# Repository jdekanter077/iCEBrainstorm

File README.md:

# iCEBrainstorm

A STM32F412 MCU with a iCE40UP5K FPGA on a compact dev board.

You will need STMCubeMX, VSCode with the STM32Cube Extension and STMCubeProgrammer to program the STM.

<!-- You can use [apio](https://github.com/FPGAwars/apio) to synthesise a design and upload the firmware to the FPGA using a [online dfu-uploader](https://devanlai.github.io/webdfu/dfu-util/) (easier) -->

<!-- You will need to use the [oss-cad-suite](https://github.com/YosysHQ/oss-cad-suite-build) to to synthesise your design and upload the bitstream to the FPGA.  -->
You can use apio to synthesize and upload your hdl on the FPGA. Refer to [apio support](#apio-support) on how to configure apio to support the iCEBrainstorm board.

## Basic Structure
The STM32 Microcontroller and the iCE40 FPGA share one PCB and have some connections between them to communicate.
They can be programmed through their respective USB-C Port.
There are some switches to select the "program mode" for both the STM and the FPGA.

The code and bootloader of the SMT are stored inside the SMT IC, but the code and bootloader of the FPGA are stored on an external SPI Flash IC. 

There is also an gyrosensor on board. For more documentation, go look at the KiCAD files.

<!--  -->

## How to Program:
Both the STM and the FPGA use a "Bootloader" to re-program themselfes. This makes the device visible to your computer and puts it in "program mode".

### STM32
The STM32 relies on its build-in bootloader to program itself via USB.
The bootloader is selected by switching the ```BOOT0``` Switch and ```RESET```-ing the SMT:
- Set the ```BOOT0``` Switch
- press ```RESET STM``` or plug in the cable
- The STM is now in DFU-mode, and can be programmed with STM32CubeProgrammer (or other software)
- In CubeProgrammer: select USB and click connect

- Click ```Open File``` and select your ```.elf``` file

- Click ```Download```

- Reset the ```BOOT0``` Switch.
- press ```RESET STM``` and your code should run.

### ICE40 FPGA

The FPGA relies on the [no2 bootloader](https://github.com/psychogenic/no2bootloader/tree/master), which is stored on the SPI-Flash IC.
The bootloader is selected by switching the ```FBOOT``` switch and ```RESET```-ing the FPGA, and then putting the ```FBOOT``` switch back.
Check if the ```CDONE``` LED at the top of the board is on.

- Set the ```FBOOT``` Switch
- press ```RESET FPGA``` or plug in the cable
- Reset the ```BOOT0``` Switch.
- Check if the ```CDONE``` LED at the top of the board is on.
- The FPGA is now in DFU-mode, and can be programmed with 
```apio upload``` or using ```dfu-util```

<!-- - run ```dfu-util -l``` to list all dfu devices. -->
<!-- example output: 
```Found DFU: [1d50:6146] ver=0006, devnum=12, cfg=1, intf=0, path="", alt=1, name="RISC-V firmware", serial="e464bc68932e5839"
Found DFU: [1d50:6146] ver=0006, devnum=12, cfg=1, intf=0, path="", alt=0, name="iCE40 bitstream", serial="e464bc68932e5839"
``` -->
<!-- - run ```dfu-util -d 1d50:6146 -a 0 -D hardware.bin``` to flash your bitstream on the FPGA. Maybe You have to replace the ```1d50:6146```-number with what you see on your terminal. -->
- you can run ```apio devices usb``` to list all dfu devices and verify that everything works.
- run ```apio upload``` to synthesize and upload the verilog code.

-  To edit your HDL code, take a look at the examples in [software/FPGA](./software/FPGA)

### APIO Support
[apio](https://github.com/FPGAwars/apio) is a open-source FPGA Toolchain, which will help us synthesize HDL code.
Make sure you have a recent version of apio installed! You can uninstall and install again to update.
- Install apio using ```pip install apio```
- edit ```~/.apio/packages/definitions/boards.jsonc``` and add this snippet:
```
  // https://github.com/jdekanter077/iCEBrainstorm
  "iCEBrainstorm": {
    "legacy-name": "iCEBrainstorm",
    "description": "iCEBrainstorm by jdk",
    "fpga-id": "ice40up5k-sg48",
    "programmer": {
      "id": "dfu"
    },
    "usb": {
      "vid": "1d50",
      "pid": "6146"
    }
  },
```

This will add apio support for the iCEBrainstorm board.
-  to create a new project, run ```apio create -b iCEBrainstorm```
-  edit your HDL code, take a look at the examples in [software/FPGA](./software/FPGA)

### Bootloader
The Bootloader is preinstalled by Joël and should not have to be touched.
Check out [bootloader/README.md](./software/FPGA/bootloader/README.md) for more information.

## Setting up a blank Project
### STM
- Open CubeMX and select ```File -> New Project```.
- In ```Commercial Part Number```, Type ```STM32F412RET6TR``` and select ```Start Project```.

- Select ```RCC_MCO_2``` on ```PB9``` to provide a Clock signal to the FPGA
- Select your desired pins, for example ```PB5```, which is connected to the on-board LED and select ```GPIO_Output```.

- On the left Pane in ```System Core -> GPIO -> PB5``` set a user label, for example ```OUT_STM```

- Set the Input Clock to Cyrstal Oscillator in ```System Core -> RCC```

- Got to ```Clock Configuration``` at the top and set the Input Frequency of the Clock to 16 MHz

- Go to ```Project Manager``` on the top.
Make sure to select ```CMake``` as the ```Toolchain / IDE```.

Make sure to set ```Generate ... as pair of '.c/.h' files ...```

- Save your project and click ```GENRATE CODE``` in the top right and open the folder in VSCode

- Make sure to not miss the notification to "configure CMake Projects as STM32 Projects". click Yes.

- Select a Preset from the Popup (Debug)
- Edit the Code, for example, add blinky loop in ```Core/Src/main.c```
- ```line 98```:

```
/* USER CODE BEGIN WHILE */
while (1)
  {
    HAL_GPIO_TogglePin(OUT_STM_GPIO_Port, OUT_STM_Pin);
    HAL_Delay(100);
    /* USER CODE END WHILE */

    /* USER CODE BEGIN 3 */
  }
  /* USER CODE END 3 */
}
```
- To Compile the code, go to ```Run & Debug -> Run & Debug -> STM32Cube: STLink GDB Server```

- This will compile the code, and try to start a "debugger", which is not available and gives a error. The Code should still be compiled correctly!
- Check if you have a ```.elf``` file in ```build/Debug/```. Upload this to the iCEBrainstorm using the steps described in [how-to-programm](#how-to-program)

## Clock
The STM and the FPGA are relatively independent from each other, with one slight caveat:
The STM32 is responsible for providing the FPGA with a Clock signal. The no2-bootloader of the FPGA relies on this clock source, and will not work without it. 

This clock can of course be used in your FPGA design as well.

### How to provide the clock 
- In cubeMX, go to ```PC9``` and select ```RCC_MCO_2```

- Generate Code, open the folder in STMCubeIDE or VSCode, compile, and upload using STMCubeProgrammer.
- Done!

## FPGA Pinout Description:
These informations should be in every ```main.pcf``` file.

| Description | FPGA Pin | Usage |
| --- | ---- | ---- |
| clk_i | 20  | 16 MHz Clock, provided by the STM32 | 
| btn_0 | 31 | left button | 
| btn_1 | 32 | right button | 
| in_0 | 34 | Input Switch and/or GPIO | 
| in_1 | 35 | Input Switch and/or GPIO | 
| in_2 | 36 | Input Switch and/or GPIO | 
| in_3 | 37 | Input Switch and/or GPIO | 
| out_0 | 25  | LED | 
| out_1 | 26  | LED | 
| out_2 | 27  | LED | 
| out_3 | 28  | LED | 
| io_0 | 47  | GPIO | 
| io_1 | 42  | GPIO | 
| io_2 | 38  | GPIO | 
| io_3 | 23  | GPIO | 
| rgb_0 | 39 | RGB LED and/or GPIO | 
| rgb_1 | 40 | RGB LED and/or GPIO | 
| rgb_2 | 41 | RGB LED and/or GPIO | 
| uart_tx | 2  | uart output (STM RX <- FPGA TX) | 
| uart_rx | 3  | uart input (STM TX -> FPGA RX) | 
| scl | 19 | I2C Clock | 
| sda | 18 | I2C Data | 

# Examples

## FPGA & STM: Morse Encoder
This project implements Morse encoder. The FPGA encodes the Morse Code, and sends the encoded character over UART to the STM.
The STM then sends the recieved character over USB to the host machine.

- upload ```./software/STM/uart_serial_bridge``` to the STM.
- upload ```./software/FPGA/morse_uart``` to the FPGA.
- open a serial monitor and have fun!

for details: take a look at the [Readme](./software/FPGA/morse_uart/README.md)

## STM: uart-serial Bridge

This project implements a UART-Serial bridge. The STM sends all recieved uart messages over usb to the host machine, and sends all recieved usb messages over usb to the FPGA.
This is done by using an Interrupt-driven approach.

snippet:

## FPGA: bram
[bram](./software/FPGA/bram)

This example of how to instintiate a one of the build-in BRAMs on the FPGA is based on [this repo](https://github.com/damdoy/ice40_ultraplus_examples/tree/master/bram) and on the [online documentation](https://www.latticesemi.com/~/media/LatticeSemi/Documents/ApplicationNotes/MO/MemoryUsageGuideforiCE40Devices.pdf)
It uses the switches IN0-IN3 as input "data" and loads it into the bram using btn0. Using btn1, the "data" can then be displayed on the leds.

# Author
Joël de Kanter

# License

This repository is primarily licensed under the GNU General Public License v3.0.

Exceptions:
- STM32CubeMX-generated files are licensed under STMicroelectronics'
  STM32Cube firmware license (see file headers).
- The NO2 bootloader firmware is licensed under GPL-3.0-or-later
- Some third-party components may be licensed under MIT or CERN OHL v2.

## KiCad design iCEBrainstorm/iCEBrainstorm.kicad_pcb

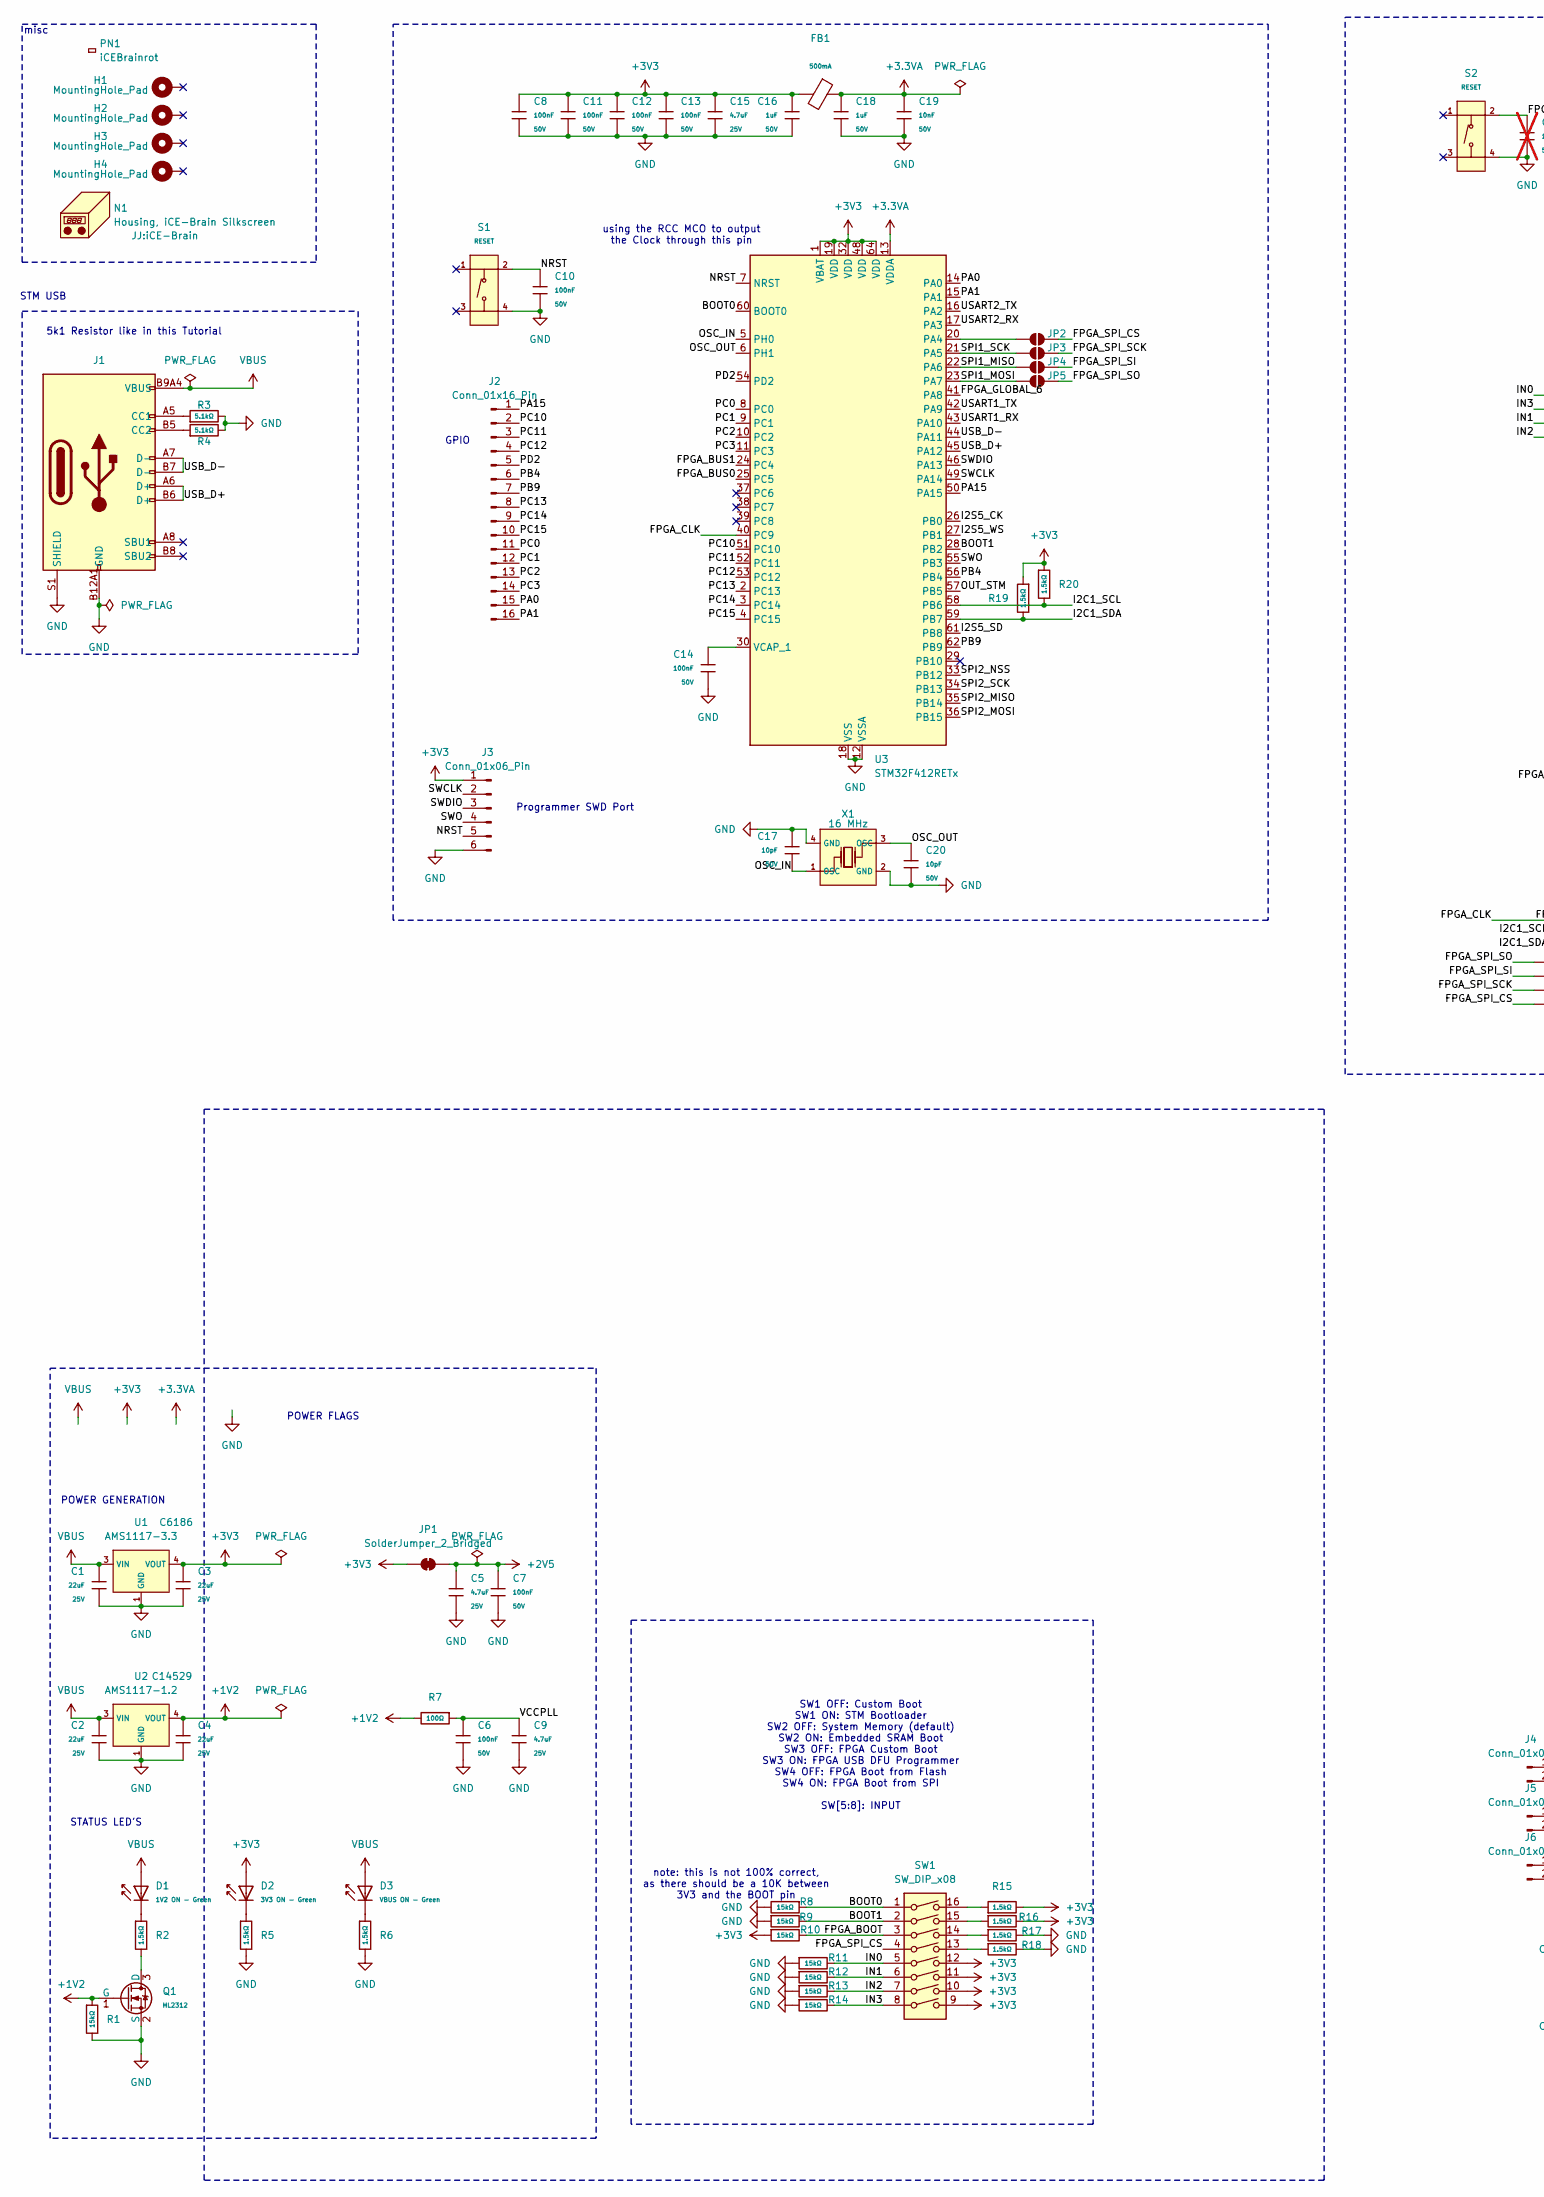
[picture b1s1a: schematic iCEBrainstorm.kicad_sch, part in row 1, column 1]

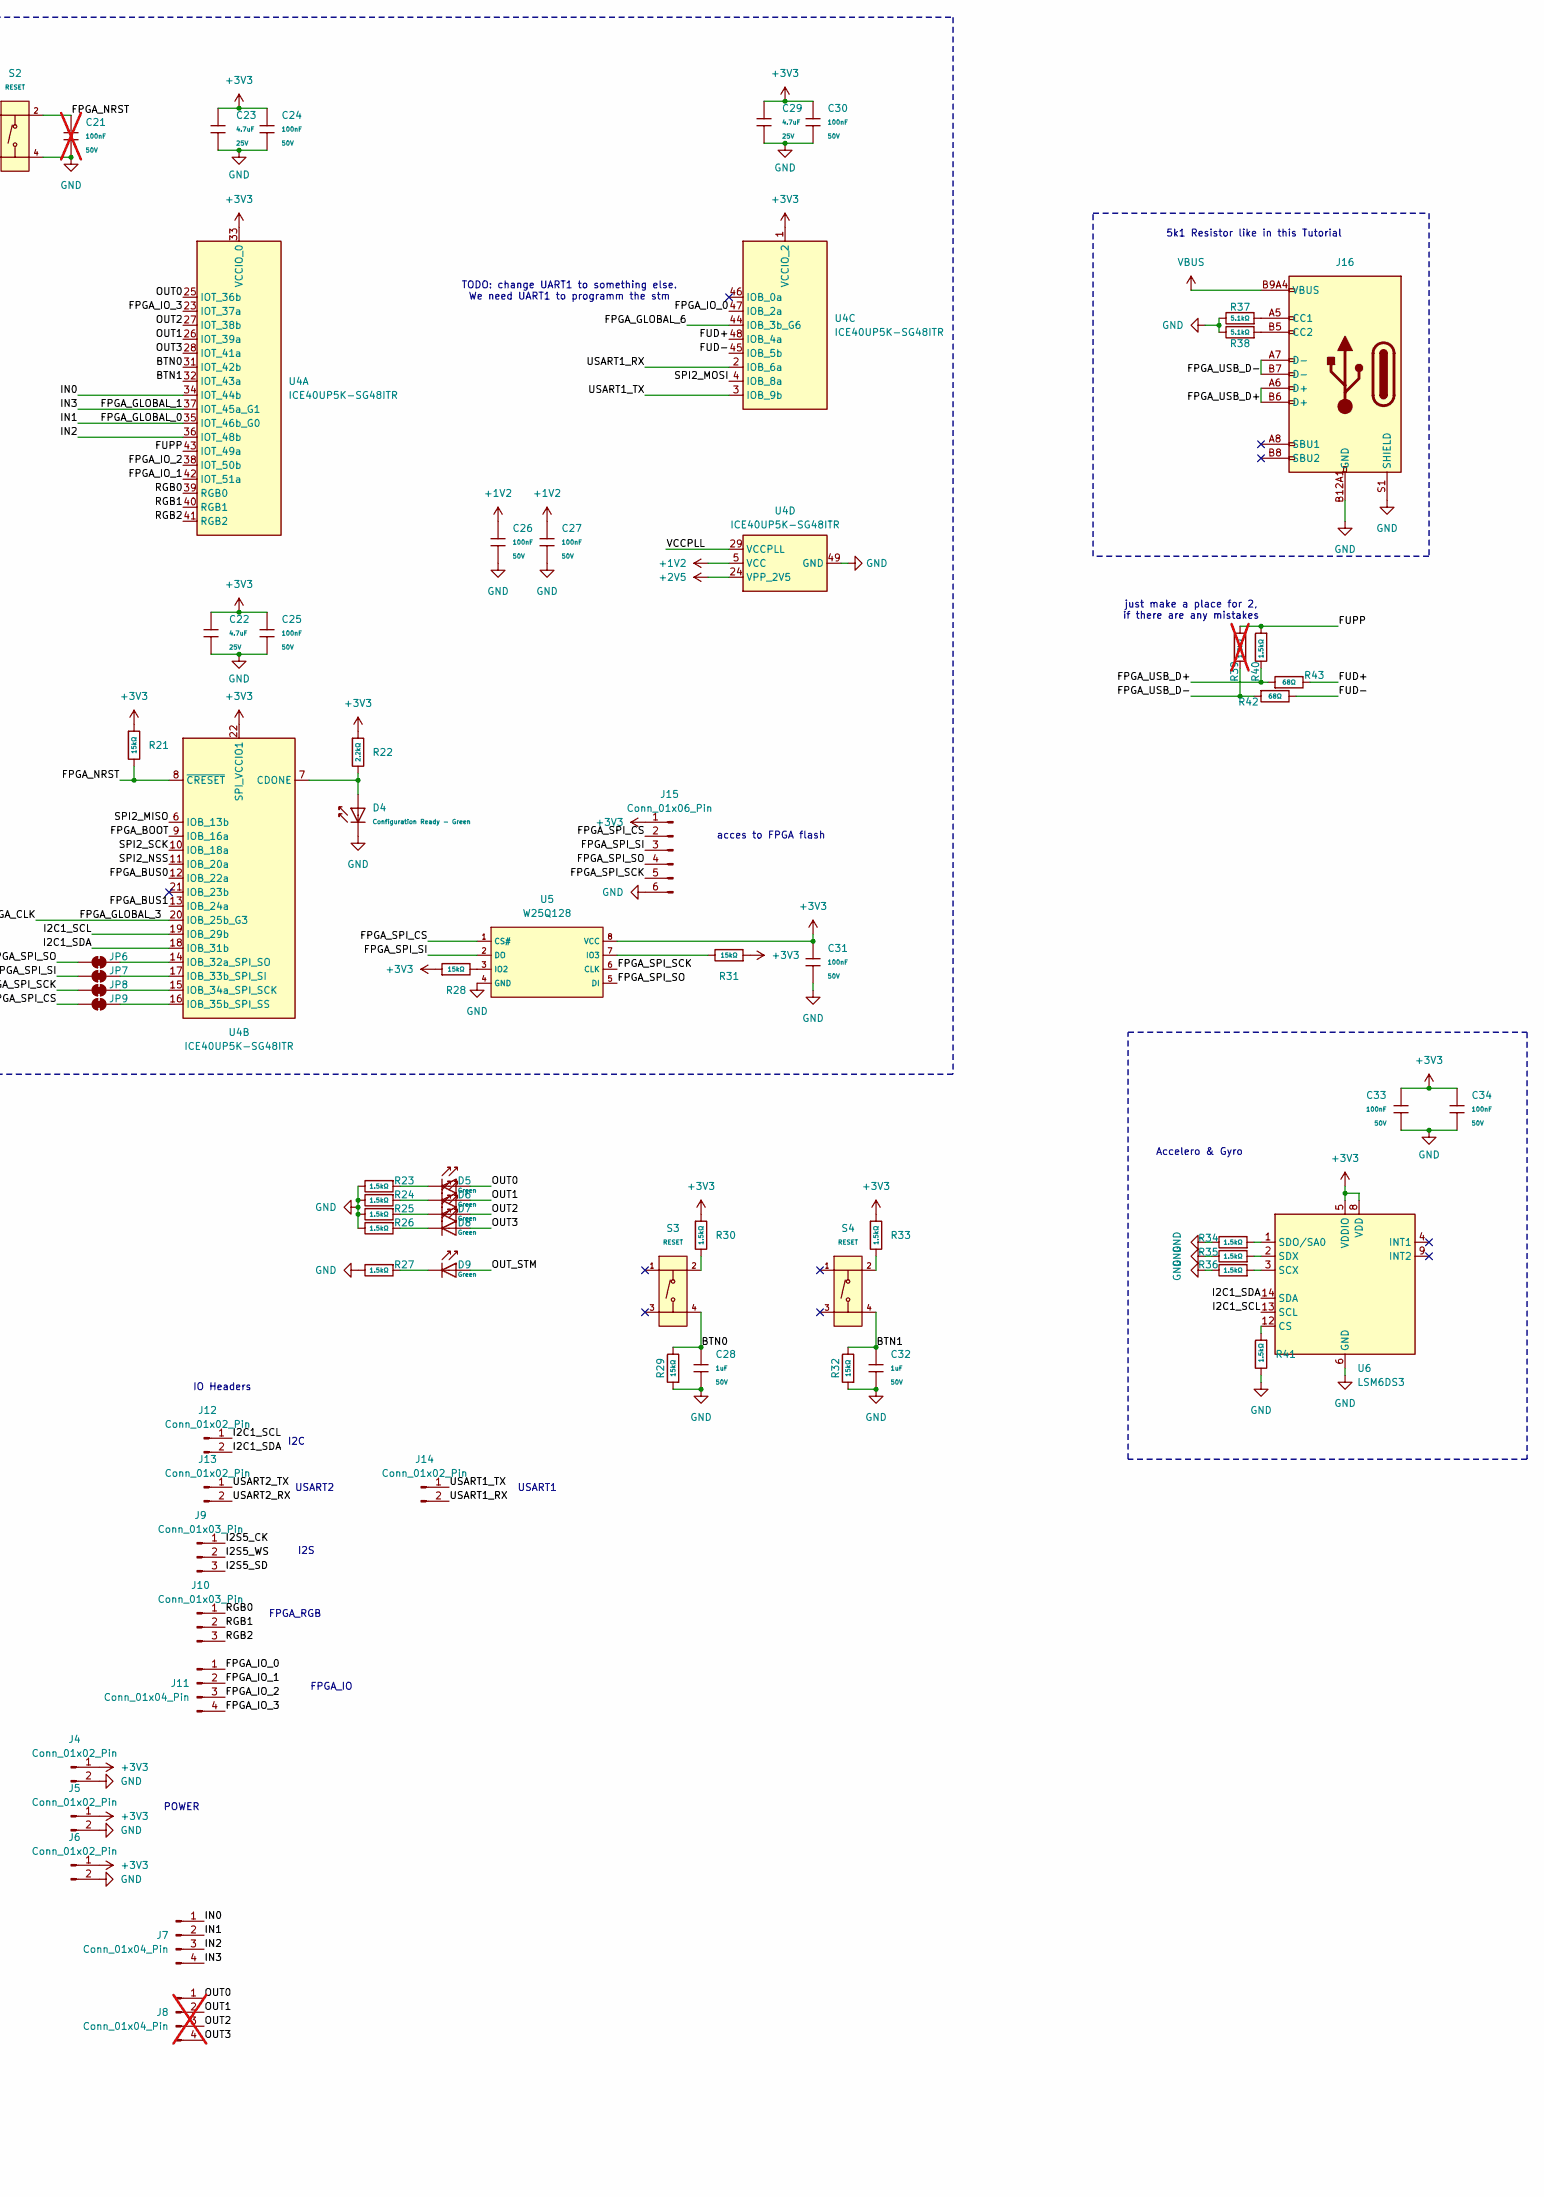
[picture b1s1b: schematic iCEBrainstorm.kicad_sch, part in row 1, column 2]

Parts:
C1, C2, C3, C4: 22uF; C_0805; Voltage Rated 25V; Tolerance ±20%; Part CL21A226MAQNNNE; LCSC C45783
C5, C9, C15, C22, C23, C29: 4.7uF; C_0805; Voltage Rated 25V; Tolerance ±10%; Part CL21A475KAQNNNE; LCSC C1779
C6, C7, C8, C10, C11, C12, C13, C14, C24, C25, C26, C27, C30, C31, C33, C34: 100nF; C_0603; Voltage Rated 50V; Tolerance ±10%; Part CC0603KRX7R9BB104; LCSC C14663
C16, C18, C28, C32: 1uF; C_0603; Voltage Rated 50V; Tolerance ±10%; Part CL10A105KB8NNNC; LCSC C15849
C17, C20: 10pF; C_0603; Voltage Rated 50V; Tolerance ±5%; Part CL10C100JB8NNNC; LCSC C1634
C19: 10nF; C_0603; Voltage Rated 50V; Tolerance ±10%; Part 0603B103K500NT; LCSC C57112
C21: 100nF; C_0603; Voltage Rated 50V; Tolerance ±10%; Part CC0603KRX7R9BB104; LCSC C14663; not fitted
D1: 1V2 ON - Green; D_0805; Part KT-0805G; LCSC C2297
D2: 3V3 ON - Green; D_0805; Part KT-0805G; LCSC C2297
D3: VBUS ON - Green; D_0805; Part KT-0805G; LCSC C2297
D4: Configuration Ready - Green; D_0805; Part KT-0805G; LCSC C2297
D5, D6, D7, D8, D9: Green; D_0805; Part KT-0805G; LCSC C2297
FB1: FB_0805; Current Rating 500mA; Tolerance ±25%; Part GZ2012D601TF; LCSC C1017
H1, H2, H3, H4: MountingHole_Pad; MountingHole_2.7mm_Pad
J1, J16: Connector, USB-TYPE-C-16P; TYPE-C-SMD_HX-TYPE-C-16PIN; LCSC C2927039
J2: Conn_01x16_Pin; PinHeader_1x16_P2.54mm_Vertical
J3, J15: Conn_01x06_Pin; PinHeader_1x06_P2.54mm_Vertical
J4, J5, J6, J12, J13, J14: Conn_01x02_Pin; PinHeader_1x02_P2.54mm_Vertical
J7, J11: Conn_01x04_Pin; PinHeader_1x04_P2.54mm_Vertical
J8: Conn_01x04_Pin; PinHeader_1x04_P2.54mm_Vertical; not fitted
J9, J10: Conn_01x03_Pin; PinHeader_1x03_P2.54mm_Vertical
JP1, JP6, JP7, JP8, JP9: SolderJumper_2_Bridged; SolderJumper-2_P1.3mm_Bridged_RoundedPad1.0x1.5mm
JP2, JP3, JP4, JP5: SolderJumper_2_Open; SolderJumper-2_P1.3mm_Open_RoundedPad1.0x1.5mm
N1: Housing, iCE-Brain Silkscreen; iCE-Brain
PN1: iCEBrainrot; Part_Num_JLCPCB
Q1: HL2312; Q_SOT-23; Part HL2312; LCSC C28646272
R1, R8, R9, R10, R11, R12, R13, R14, R21, R28, R29, R31, R32: 15kΩ; R_0603; Overload Voltage (Max) 75V; Tolerance ±1%; Part 0603WAF1502T5E; LCSC C22809
R2, R5, R6, R15, R16, R17, R18, R19, R20, R23, R24, R25, R26, R27, R30, R33, R34, R35, R36, R40, R41: 1.5kΩ; R_0603; Overload Voltage (Max) 75V; Tolerance ±1%; Part 0603WAF1501T5E; LCSC C22843
R3, R4, R37, R38: 5.1kΩ; R_0603; Overload Voltage (Max) 75V; Tolerance ±1%; Part 0603WAF5101T5E; LCSC C23186
R7: 100Ω; R_0603; Overload Voltage (Max) 75V; Tolerance ±1%; Part 0603WAF1000T5E; LCSC C22775
R22: 2.2kΩ; R_0603; Overload Voltage (Max) 75V; Tolerance ±1%; Part 0603WAF2201T5E; LCSC C4190
R39: 1.5kΩ; R_0603; Overload Voltage (Max) 75V; Tolerance ±1%; Part 0603WAF1501T5E; LCSC C22843; not fitted
R42, R43: 68Ω; R_0603; Overload Voltage (Max) 75V; Tolerance ±1%; Part 0603WAF680JT5E; LCSC C27592
S1, S2, S3, S4: RESET; SW-SMD_4P-L5.1-W5.1-P3.70-LS6.5-TL-2; Voltage Rating (Dc) 12V; Part TS-1187A-B-A-B; LCSC C318884
SW1: SW_DIP_x08; SW_DIP_SPSTx08_Slide_6.7x21.88mm_W7.62mm_P2.54mm_LowProfile
U1: AMS1117-3.3; SOT-223-3_L6.5-W3.4-P2.30-LS7.0-BR; Output Voltage 3.3V; Dropout Voltage 1.3V@(800mA); Part AMS1117-3.3; LCSC C6186
U2: AMS1117-1.2; SOT-223-3_L6.5-W3.4-P2.30-LS7.0-BR; Output Voltage 3.3V; Dropout Voltage 1.3V@(800mA); Part AMS1117-3.3; LCSC C14529
U3: STM32F412RETx; LQFP-64_10x10mm_P0.5mm
U4: ICE40UP5K-SG48ITR; QFN-48-1EP_7x7mm_P0.5mm_EP5.6x5.6mm
U5: W25Q128; SOIC-8_L5.3-W5.3-P1.27-LS8.0-BL; Part W25Q128JVSIQ; LCSC C97521
U6: LSM6DS3; LGA-14_3x2.5mm_P0.5mm_LayoutBorder3x4y
X1: 16 MHz; OSC-SMD_4P-L3.2-W2.5-BL; Frequency Tolerance ±10ppm; Part X322516MLB4SI; LCSC C13738

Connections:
+1V2: C4.2, C26.1, C27.1, Q1.1 (G), R1.1, R7.2, U2.2 (VOUT), U2.4 (VOUT), U4.5 (VCC), U4.30 (VCC)
+2V5: C5.1, C7.1, JP1.2 (B), U4.24 (VPP_2V5)
+3.3VA: C18.1, C19.1, FB1.1, U3.13 (VDDA)
+3V3: C3.2, C8.1, C11.1, C12.1, C13.1, C15.1, C16.1, C22.1, C23.1, C24.1, C25.1, C29.1, C30.1, C31.1, C33.1, C34.1, D2.2, FB1.2, J3.1, J4.1, J5.1, J6.1, J15.1, JP1.1 (A), R10.1, R15.2, R16.2, R19.1, R20.1, R21.1, R22.1, R28.1, R30.1, R31.1, R33.1, SW1.9, SW1.10, SW1.11, SW1.12, U1.2 (VOUT), U1.4 (VOUT), U3.1 (VBAT), U3.19 (VDD), U3.32 (VDD), U3.48 (VDD), U3.64 (VDD), U4.1 (VCCIO_2), U4.22 (SPI_VCCIO1), U4.33 (VCCIO_0), U5.8 (VCC), U6.5 (VDDIO), U6.8 (VDD)
/BOOT0: R8.1, SW1.1, U3.60 (BOOT0)
/BOOT1: R9.2, SW1.2, U3.28 (PB2)
/BTN0: C28.1, R29.2, S3.4 (D), U4.31 (IOT_42b)
/BTN1: C32.1, R32.2, S4.4 (D), U4.32 (IOT_43a)
/FPGA_BOOT: R10.2, SW1.3, U4.9 (IOB_16a)
/FPGA_BUS0: U3.25 (PC5), U4.12 (IOB_22a)
/FPGA_BUS1: U3.24 (PC4), U4.13 (IOB_24a)
/FPGA_CLK: U3.40 (PC9), U4.20 (IOB_25b_G3)
/FPGA_GLOBAL_0: J7.2, R12.2, SW1.6, U4.35 (IOT_46b_G0)
/FPGA_GLOBAL_1: J7.4, R14.2, SW1.8, U4.37 (IOT_45a_G1)
/FPGA_GLOBAL_6: U3.41 (PA8), U4.44 (IOB_3b_G6)
/FPGA_IO_0: J11.1, U4.47 (IOB_2a)
/FPGA_IO_1: J11.2, U4.42 (IOT_51a)
/FPGA_IO_2: J11.3, U4.38 (IOT_50b)
/FPGA_IO_3: J11.4, U4.23 (IOT_37a)
/FPGA_NRST: C21.1, R21.2, S2.2 (B), U4.8 (~CRESET)
/FPGA_SPI_CS: J15.2, JP2.2 (B), JP9.1 (A), SW1.4, U5.1 (CS#)
/FPGA_SPI_SCK: J15.5, JP3.2 (B), JP8.1 (A), U5.6 (CLK)
/FPGA_SPI_SI: J15.3, JP4.2 (B), JP7.1 (A), U5.2 (DO)
/FPGA_SPI_SO: J15.4, JP5.2 (B), JP6.1 (A), U5.5 (DI)
/FPGA_USB_D+: J16.A6 (D+), J16.B6 (D+), R40.2, R43.1
/FPGA_USB_D-: J16.A7 (D-), J16.B7 (D-), R39.2, R42.1
/FUD+: R43.2, U4.48 (IOB_4a)
/FUD-: R42.2, U4.45 (IOB_5b)
/FUPP: R39.1, R40.1, U4.43 (IOT_49a)
/I2C1_SCL: J12.1, R20.2, U3.58 (PB6), U4.19 (IOB_29b), U6.13 (SCL)
/I2C1_SDA: J12.2, R19.2, U3.59 (PB7), U4.18 (IOB_31b), U6.14 (SDA)
/I2S5_CK: J9.1, U3.26 (PB0)
/I2S5_SD: J9.3, U3.61 (PB8)
/I2S5_WS: J9.2, U3.27 (PB1)
/IN0: J7.1, R11.2, SW1.5, U4.34 (IOT_44b)
/IN2: J7.3, R13.2, SW1.7, U4.36 (IOT_48b)
/NRST: C10.1, J3.5, S1.2 (B), U3.7 (NRST)
/OSC_IN: C17.2, U3.5 (PH0), X1.1 (OSC)
/OSC_OUT: C20.1, U3.6 (PH1), X1.3 (OSC)
/OUT0: D5.2, J8.1, U4.25 (IOT_36b)
/OUT1: D6.2, J8.2, U4.26 (IOT_39a)
/OUT2: D7.2, J8.3, U4.27 (IOT_38b)
/OUT3: D8.2, J8.4, U4.28 (IOT_41a)
/OUT_STM: D9.2, U3.57 (PB5)
/PA0: J2.15, U3.14 (PA0)
/PA1: J2.16, U3.15 (PA1)
/PA15: J2.1, U3.50 (PA15)
/PB4: J2.6, U3.56 (PB4)
/PB9: J2.7, U3.62 (PB9)
/PC0: J2.11, U3.8 (PC0)
/PC1: J2.12, U3.9 (PC1)
/PC2: J2.13, U3.10 (PC2)
/PC3: J2.14, U3.11 (PC3)
/PC10: J2.2, U3.51 (PC10)
/PC11: J2.3, U3.52 (PC11)
/PC12: J2.4, U3.53 (PC12)
/PC13: J2.8, U3.2 (PC13)
/PC14: J2.9, U3.3 (PC14)
/PC15: J2.10, U3.4 (PC15)
/PD2: J2.5, U3.54 (PD2)
/RGB0: J10.1, U4.39 (RGB0)
/RGB1: J10.2, U4.40 (RGB1)
/RGB2: J10.3, U4.41 (RGB2)
/SPI1_MISO: JP4.1 (A), U3.22 (PA6)
/SPI1_MOSI: JP5.1 (A), U3.23 (PA7)
/SPI1_SCK: JP3.1 (A), U3.21 (PA5)
/SPI2_MISO: U3.35 (PB14), U4.6 (IOB_13b)
/SPI2_MOSI: U3.36 (PB15), U4.4 (IOB_8a)
/SPI2_NSS: U3.33 (PB12), U4.11 (IOB_20a)
/SPI2_SCK: U3.34 (PB13), U4.10 (IOB_18a)
/SWCLK: J3.2, U3.49 (PA14)
/SWDIO: J3.3, U3.46 (PA13)
/SWO: J3.4, U3.55 (PB3)
/USART1_RX: J14.2, U3.43 (PA10), U4.2 (IOB_6a)
/USART1_TX: J14.1, U3.42 (PA9), U4.3 (IOB_9b)
/USART2_RX: J13.2, U3.17 (PA3)
/USART2_TX: J13.1, U3.16 (PA2)
/USB_D+: J1.A6 (D+), J1.B6 (D+), U3.45 (PA12)
/USB_D-: J1.A7 (D-), J1.B7 (D-), U3.44 (PA11)
/VCCPLL: C6.1, C9.1, R7.1, U4.29 (VCCPLL)
GND: C1.1, C2.1, C3.1, C4.1, C5.2, C6.2, C7.2, C8.2, C9.2, C10.2, C11.2, C12.2, C13.2, C14.1, C15.2, C16.2, C17.1, C18.2, C19.2, C20.2, C21.2, C22.2, C23.2, C24.2, C25.2, C26.2, C27.2, C28.2, C29.2, C30.2, C31.2, C32.2, C33.2, C34.2, D4.1, J1.A12B1 (GND), J1.B12A1 (GND), J1.S1 (SHIELD), J3.6, J4.2, J5.2, J6.2, J15.6, J16.A12B1 (GND), J16.B12A1 (GND), J16.S1 (SHIELD), Q1.2 (S), R1.2, R3.2, R4.2, R5.2, R6.2, R8.2, R9.1, R11.1, R12.1, R13.1, R14.1, R17.2, R18.2, R23.2, R24.2, R25.2, R26.2, R27.2, R29.1, R32.1, R34.2, R35.2, R36.2, R37.2, R38.2, R41.2, S1.4 (D), S2.4 (D), U1.1 (GND), U2.1 (GND), U3.12 (VSSA), U3.18 (VSS), U3.31 (VSS), U3.47 (VSS), U3.63 (VSS), U4.49 (GND), U5.4 (GND), U6.6 (GND), U6.7 (GND), X1.2 (GND), X1.4 (GND)
unnamed: D1.1, R2.1
unnamed: D2.1, R5.1
unnamed: D3.1, R6.1
unnamed: D5.1, R23.1
unnamed: D6.1, R24.1
unnamed: D7.1, R25.1
unnamed: D8.1, R26.1
unnamed: D9.1, R27.1
unnamed: J1.A5 (CC1), R3.1
unnamed: J1.B5 (CC2), R4.1
unnamed: J16.A5 (CC1), R37.1
unnamed: J16.B5 (CC2), R38.1
unnamed: JP2.1 (A), U3.20 (PA4)
unnamed: JP6.2 (B), U4.14 (IOB_32a_SPI_SO)
unnamed: JP7.2 (B), U4.17 (IOB_33b_SPI_SI)
unnamed: JP8.2 (B), U4.15 (IOB_34a_SPI_SCK)
unnamed: JP9.2 (B), U4.16 (IOB_35b_SPI_SS)
unnamed: Q1.3 (D), R2.2
unnamed: R15.1, SW1.16
unnamed: R16.1, SW1.15
unnamed: R17.1, SW1.14
unnamed: R18.1, SW1.13
unnamed: R30.2, S3.2 (B)
unnamed: R33.2, S4.2 (B)
unnamed: C14.2, U3.30 (VCAP_1)
unnamed: D4.2, R22.2, U4.7 (CDONE)
unnamed: R28.2, U5.3 (IO2)
unnamed: R31.2, U5.7 (IO3)
unnamed: R41.1, U6.12 (CS)
unnamed: R36.1, U6.3 (SCX)
unnamed: R34.1, U6.1 (SDO/SA0)
unnamed: R35.1, U6.2 (SDX)
VBUS: C1.2, C2.2, D1.2, D3.2, J1.A9B4 (VBUS), J1.B9A4 (VBUS), J16.A9B4 (VBUS), J16.B9A4 (VBUS), U1.3 (VIN), U2.3 (VIN)

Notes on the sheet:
GPIO
POWER GENERATION
acces to FPGA flash
FPGA_IO
Programmer SWD Port
misc
I2S
IO Headers
5k1 Resistor like in this Tutorial
TODO: change UART1 to something else. We need UART1 to programm the stm
I2C
USART2
Accelero & Gyro
POWER FLAGS
note: this is not 100% correct, as there should be a 10K between 3V3 and the BOOT pin
FPGA_RGB
just make a place for 2, if there are any mistakes
STATUS LED'S
SW1 OFF: Custom Boot SW1 ON: STM Bootloader SW2 OFF: System Memory (default) SW2 ON: Embedded SRAM Boot SW3 OFF: FPGA Custom Boot SW3 ON: FPGA USB DFU Programmer SW4 OFF: FPGA Boot from Flash SW4 ON: FPGA Boot from SPI SW[5:8]: INPUT
POWER
STM USB
USART1
using the RCC MCO to output the Clock through this pin

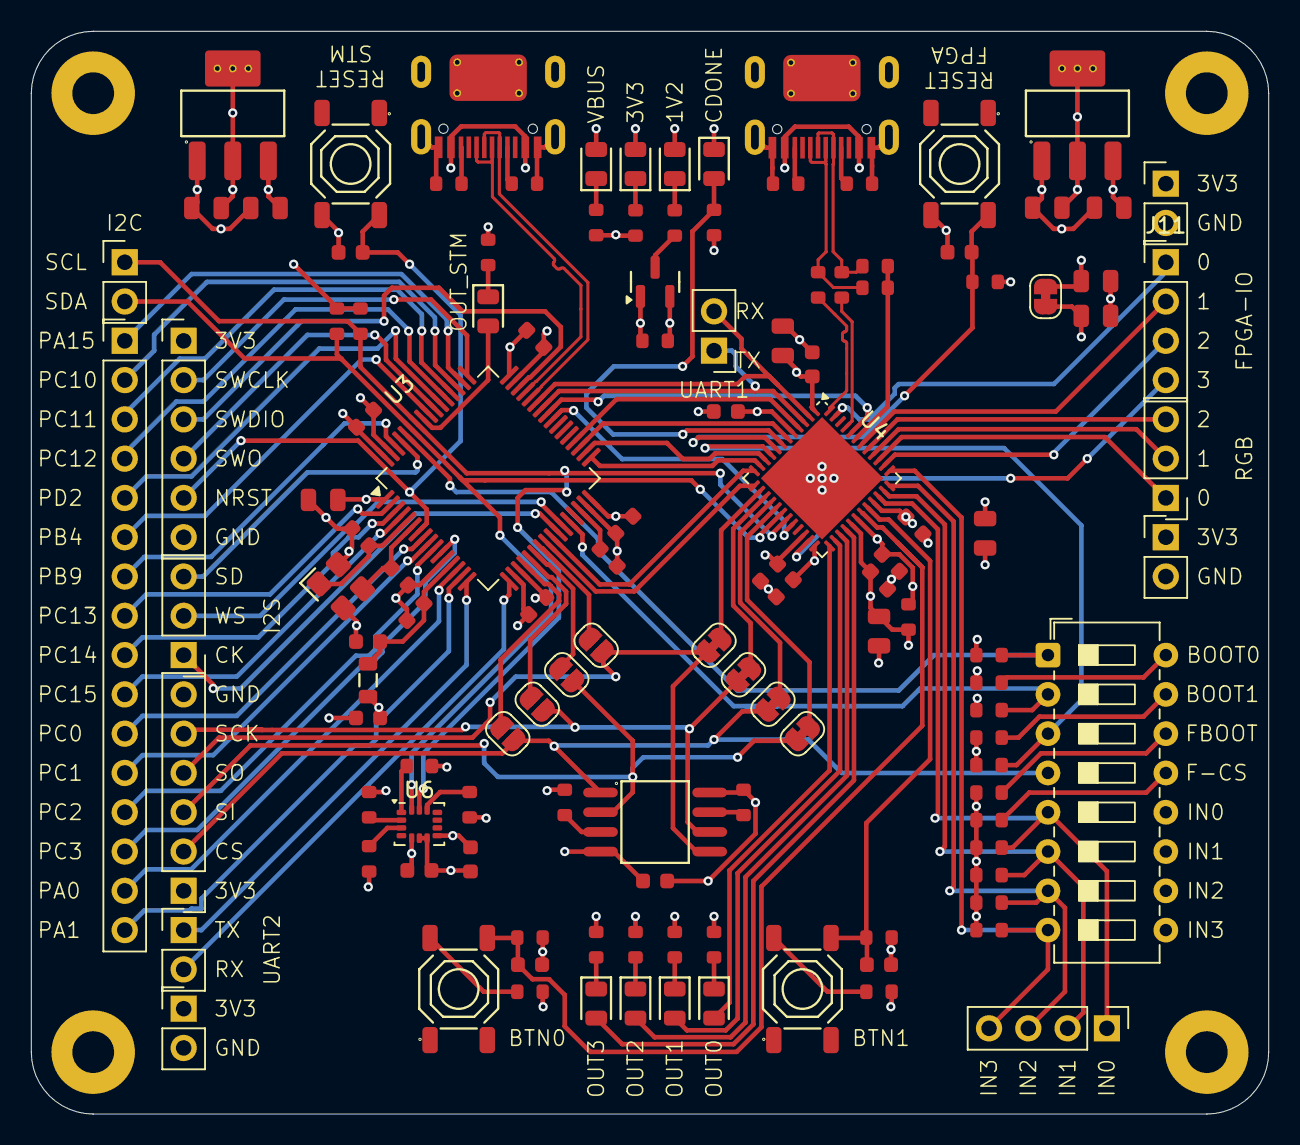
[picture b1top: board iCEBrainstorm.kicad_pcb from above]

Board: 4 copper layers, 80.0 x 70.0 mm, 130 parts (1 on the bottom side), 114 nets.

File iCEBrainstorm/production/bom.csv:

Designator,Footprint,Quantity,Value,LCSC Part #
"C1, C2, C3, C4",C_0805,4,22uF,C45783
"C10, C11, C12, C13, C14, C24, C25, C26, C27, C30, C31, C33, C34, C6, C7, C8",C_0603,16,100nF,C14663
"C15, C22, C23, C29, C5, C9",C_0805,6,4.7uF,C1779
"C16, C18, C28, C32",C_0603,4,1uF,C15849
"C17, C20",C_0603,2,10pF,C1634
C19,C_0603,1,10nF,C57112
D1,D_0805,1,1V2 ON - Green,C2297
D2,D_0805,1,3V3 ON - Green,C2297
D3,D_0805,1,VBUS ON - Green,C2297
D4,D_0805,1,Configuration Ready - Green,C2297
"D5, D6, D7, D8, D9",D_0805,5,Green,C2297
FB1,FB_0805,1,~,C1017
"J1, J16",TYPE-C-SMD_HX-TYPE-C-16PIN,2,"Connector, USB-TYPE-C-16P",C2927039
"J10, J9",PinHeader_1x03_P2.54mm_Vertical,2,Conn_01x03_Pin,
"J11, J7",PinHeader_1x04_P2.54mm_Vertical,2,Conn_01x04_Pin,
"J12, J13, J14, J4, J5, J6",PinHeader_1x02_P2.54mm_Vertical,6,Conn_01x02_Pin,
"J15, J3",PinHeader_1x06_P2.54mm_Vertical,2,Conn_01x06_Pin,
J2,PinHeader_1x16_P2.54mm_Vertical,1,Conn_01x16_Pin,
N1,iCE-Brain,1,"Housing, iCE-Brain Silkscreen",
PN1,Part_Num_JLCPCB,1,iCEBrainrot,
Q1,Q_SOT-23,1,HL2312,C28646272
"R1, R10, R11, R12, R13, R14, R21, R28, R29, R31, R32, R8, R9",R_0603,13,15kΩ,C22809
"R15, R16, R17, R18, R19, R2, R20, R23, R24, R25, R26, R27, R30, R33, R34, R35, R36, R40, R41, R5, R6",R_0603,21,1.5kΩ,C22843
R22,R_0603,1,2.2kΩ,C4190
"R3, R37, R38, R4",R_0603,4,5.1kΩ,C23186
"R42, R43",R_0603,2,68Ω,C27592
R7,R_0603,1,100Ω,C22775
"S1, S2, S3, S4",SW-SMD_4P-L5.1-W5.1-P3.70-LS6.5-TL-2,4,RESET,C318884
SW1,SW_DIP_SPSTx08_Slide_6.7x21.88mm_W7.62mm_P2.54mm_LowProfile,1,SW_DIP_x08,
U1,SOT-223-3_L6.5-W3.4-P2.30-LS7.0-BR,1,AMS1117-3.3,C6186
U2,SOT-223-3_L6.5-W3.4-P2.30-LS7.0-BR,1,AMS1117-1.2,C14529
U3,LQFP-64_10x10mm_P0.5mm,1,STM32F412RETx,C89374
U4,QFN-48-1EP_7x7mm_P0.5mm_EP5.6x5.6mm,1,ICE40UP5K-SG48ITR,C2678152
U5,SOIC-8_L5.3-W5.3-P1.27-LS8.0-BL,1,W25Q128,C97521
U6,LGA-14_3x2.5mm_P0.5mm_LayoutBorder3x4y,1,LSM6DS3,
X1,OSC-SMD_4P-L3.2-W2.5-BL,1,16 MHz,C13738

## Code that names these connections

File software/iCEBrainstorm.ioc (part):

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Mcu.Name=STM32F412R(E-G)Tx
Mcu.Package=LQFP64
Mcu.UserName=STM32F412RETx
PA10.Mode=Asynchronous
PA10.Signal=USART1_RX
PA11.Mode=Device_Only
PA11.Signal=USB_OTG_FS_DM
PA12.Mode=Device_Only
PA12.Signal=USB_OTG_FS_DP
PA13.Signal=SYS_JTMS-SWDIO
PA14.Signal=SYS_JTCK-SWCLK
PA2.Mode=Asynchronous
PA2.Signal=USART2_TX
PA3.Mode=Asynchronous
PA3.Signal=USART2_RX
PA5.Mode=Full_Duplex_Master
PA5.Signal=SPI1_SCK
PA6.Mode=Full_Duplex_Master
PA6.Signal=SPI1_MISO
PA7.Mode=Full_Duplex_Master
PA7.Signal=SPI1_MOSI
PA9.Mode=Asynchronous
PA9.Signal=USART1_TX
PB0.Mode=Half_Duplex_Master
PB0.Signal=I2S5_CK
PB1.Mode=Half_Duplex_Master
PB1.Signal=I2S5_WS
PB12.Mode=NSS_Signal_Hard_Output
PB12.Signal=SPI2_NSS
PB13.Mode=Full_Duplex_Master
PB13.Signal=SPI2_SCK
PB14.Mode=Full_Duplex_Master
PB14.Signal=SPI2_MISO
PB15.Mode=Full_Duplex_Master
PB15.Signal=SPI2_MOSI
PB3.Signal=SYS_JTDO-SWO
PB6.Mode=I2C
PB6.Signal=I2C1_SCL
PB7.Mode=I2C
PB7.Signal=I2C1_SDA
PB8.Mode=Half_Duplex_Master
PB8.Signal=I2S5_SD
PC9.Mode=Clock-out-2
PC9.Signal=RCC_MCO_2
PH0\ -\ OSC_IN.Mode=HSE-External-Oscillator
PH0\ -\ OSC_IN.Signal=RCC_OSC_IN
PH1\ -\ OSC_OUT.Mode=HSE-External-Oscillator
PH1\ -\ OSC_OUT.Signal=RCC_OSC_OUT
RCC.HSE_VALUE=25000000
board=custom

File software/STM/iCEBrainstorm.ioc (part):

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Mcu.Name=STM32F412R(E-G)Tx
Mcu.Package=LQFP64
Mcu.UserName=STM32F412RETx
PA11.Mode=Device_Only
PA11.Signal=USB_OTG_FS_DM
PA12.Mode=Device_Only
PA12.Signal=USB_OTG_FS_DP
PA13.Signal=SYS_JTMS-SWDIO
PA14.Signal=SYS_JTCK-SWCLK
PA2.Mode=Asynchronous
PA2.Signal=USART2_TX
PA3.Mode=Asynchronous
PA3.Signal=USART2_RX
PB12.Signal=SPI2_NSS
PB13.Signal=SPI2_SCK
PB14.Signal=SPI2_MISO
PB15.Signal=SPI2_MOSI
PB3.Signal=SYS_JTDO-SWO
PB5.GPIOParameters=GPIO_Label
PB5.GPIO_Label=OUT_STM
PB5.Signal=GPIO_Output
PC9.Mode=Clock-out-2
PC9.Signal=RCC_MCO_2
PH0\ -\ OSC_IN.Mode=HSE-External-Oscillator
PH0\ -\ OSC_IN.Signal=RCC_OSC_IN
PH1\ -\ OSC_OUT.Mode=HSE-External-Oscillator
PH1\ -\ OSC_OUT.Signal=RCC_OSC_OUT
RCC.HSE_VALUE=25000000
board=custom

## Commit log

2025-10-30 init and playing around with jlcpcb plugins...
2025-11-02 commit from within kicad
2025-11-04 added some things to schematic
2025-11-20 did some things
2025-11-23 schema und pcb gmacht, quote kostet jetzt 120$ / 10 pcs
2025-11-25 pascuu design review
2025-11-26 finalised the schematic
2025-11-27 still checking schematic
2025-11-27 did some placment
2025-12-01 lets push
2025-12-01 cleared up a bit
2025-12-01 gekocht mit luci
2025-12-02 merged ueberarbeiten
2025-12-02 wider mit luci gekocht
2025-12-06 did some lines + added a IN connector :)
2025-12-07 did back silkscreen design
2025-12-10 added uart1 connector, added power connectors, added schema back silkscreen symbol
2025-12-11 did some routing
2025-12-11 fertig
2025-12-11 preparing for order, need to change some components...
2025-12-11 send to production, note that the SM6DS3TR got replaced with the LSM6DSRTR for cost reasons.
2025-12-14 cleaned up the folder
2025-12-14 more structure
2025-12-14 added README
2025-12-29 added STM and FPGA Code, added bootloader binairy, did more documentation
2025-12-29 added licence
2025-12-29 Create LICENSE
2026-01-06 added no2bootloader as submodule and added documentation on how to buzild the bootloader and flash the SPI flash
2026-01-06 again.
2026-01-06 did some more docu
2026-01-12 more docu
2026-01-18 added a FPGA autocounter example, added Makefile script
2026-01-20 added apio documentation
2026-01-21 added blinky
2026-01-28 updated FPGA counter example and make STM blinky2
2026-01-28 added in morse_uart and deleted its git folder....
2026-01-28 changed the STM USB-UART Bridge
2026-01-28 updated readme for morse project info
2026-02-11 updated readme: added stm32 project setup tutorial
2026-02-23 init bram example, didn't work so far
2026-03-15 fixed bram and added it to documentation
